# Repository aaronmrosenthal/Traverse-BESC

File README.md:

# TRAVERSE VESC
alpha controller

Based on BESC-G2 VESC

TRAVERSE VESC is licensed under the Creative Commons Attribution-ShareAlike 4.0 International License. To view a copy of this license, visit http://creativecommons.org/licenses/by-sa/4.0/.

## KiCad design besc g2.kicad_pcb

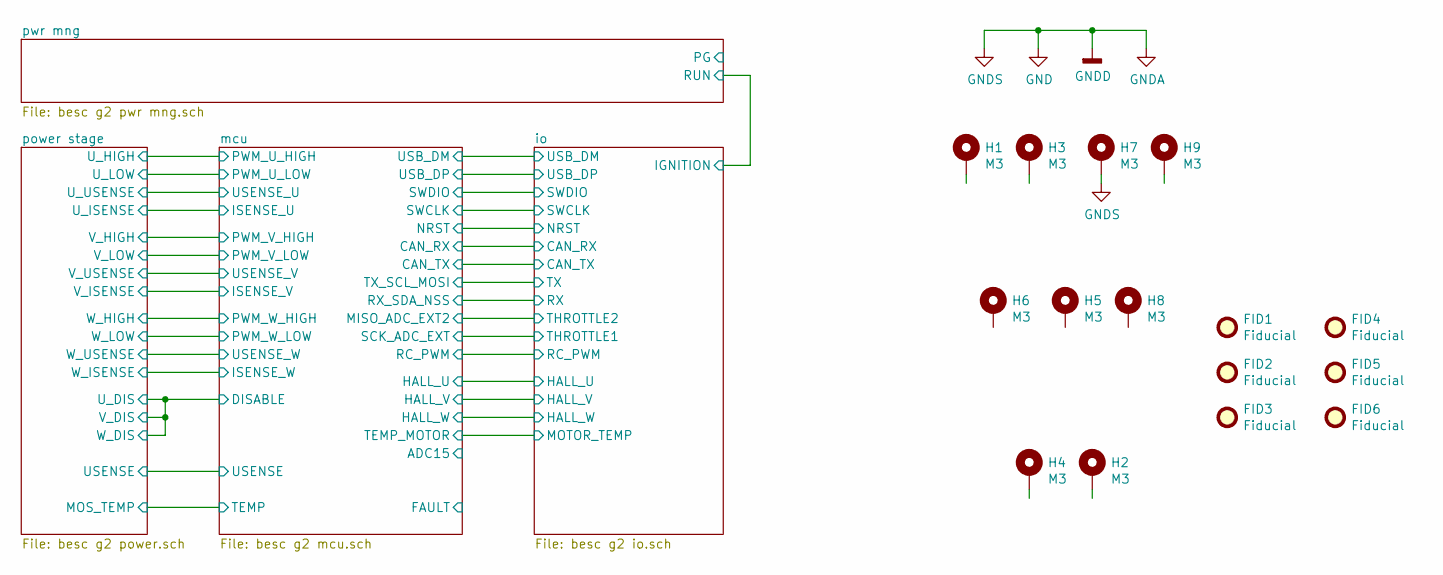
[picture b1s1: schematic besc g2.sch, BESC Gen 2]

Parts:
FID1, FID2, FID3, FID4, FID5, FID6: Fiducial; Fiducial_0.5mm_Mask1.5mm
H1, H2, H3, H4, H5, H6, H7, H8, H9: M3; MountingHole_3.2mm_M3_Pad_Via

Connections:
GND: H7.1; also elsewhere on the board

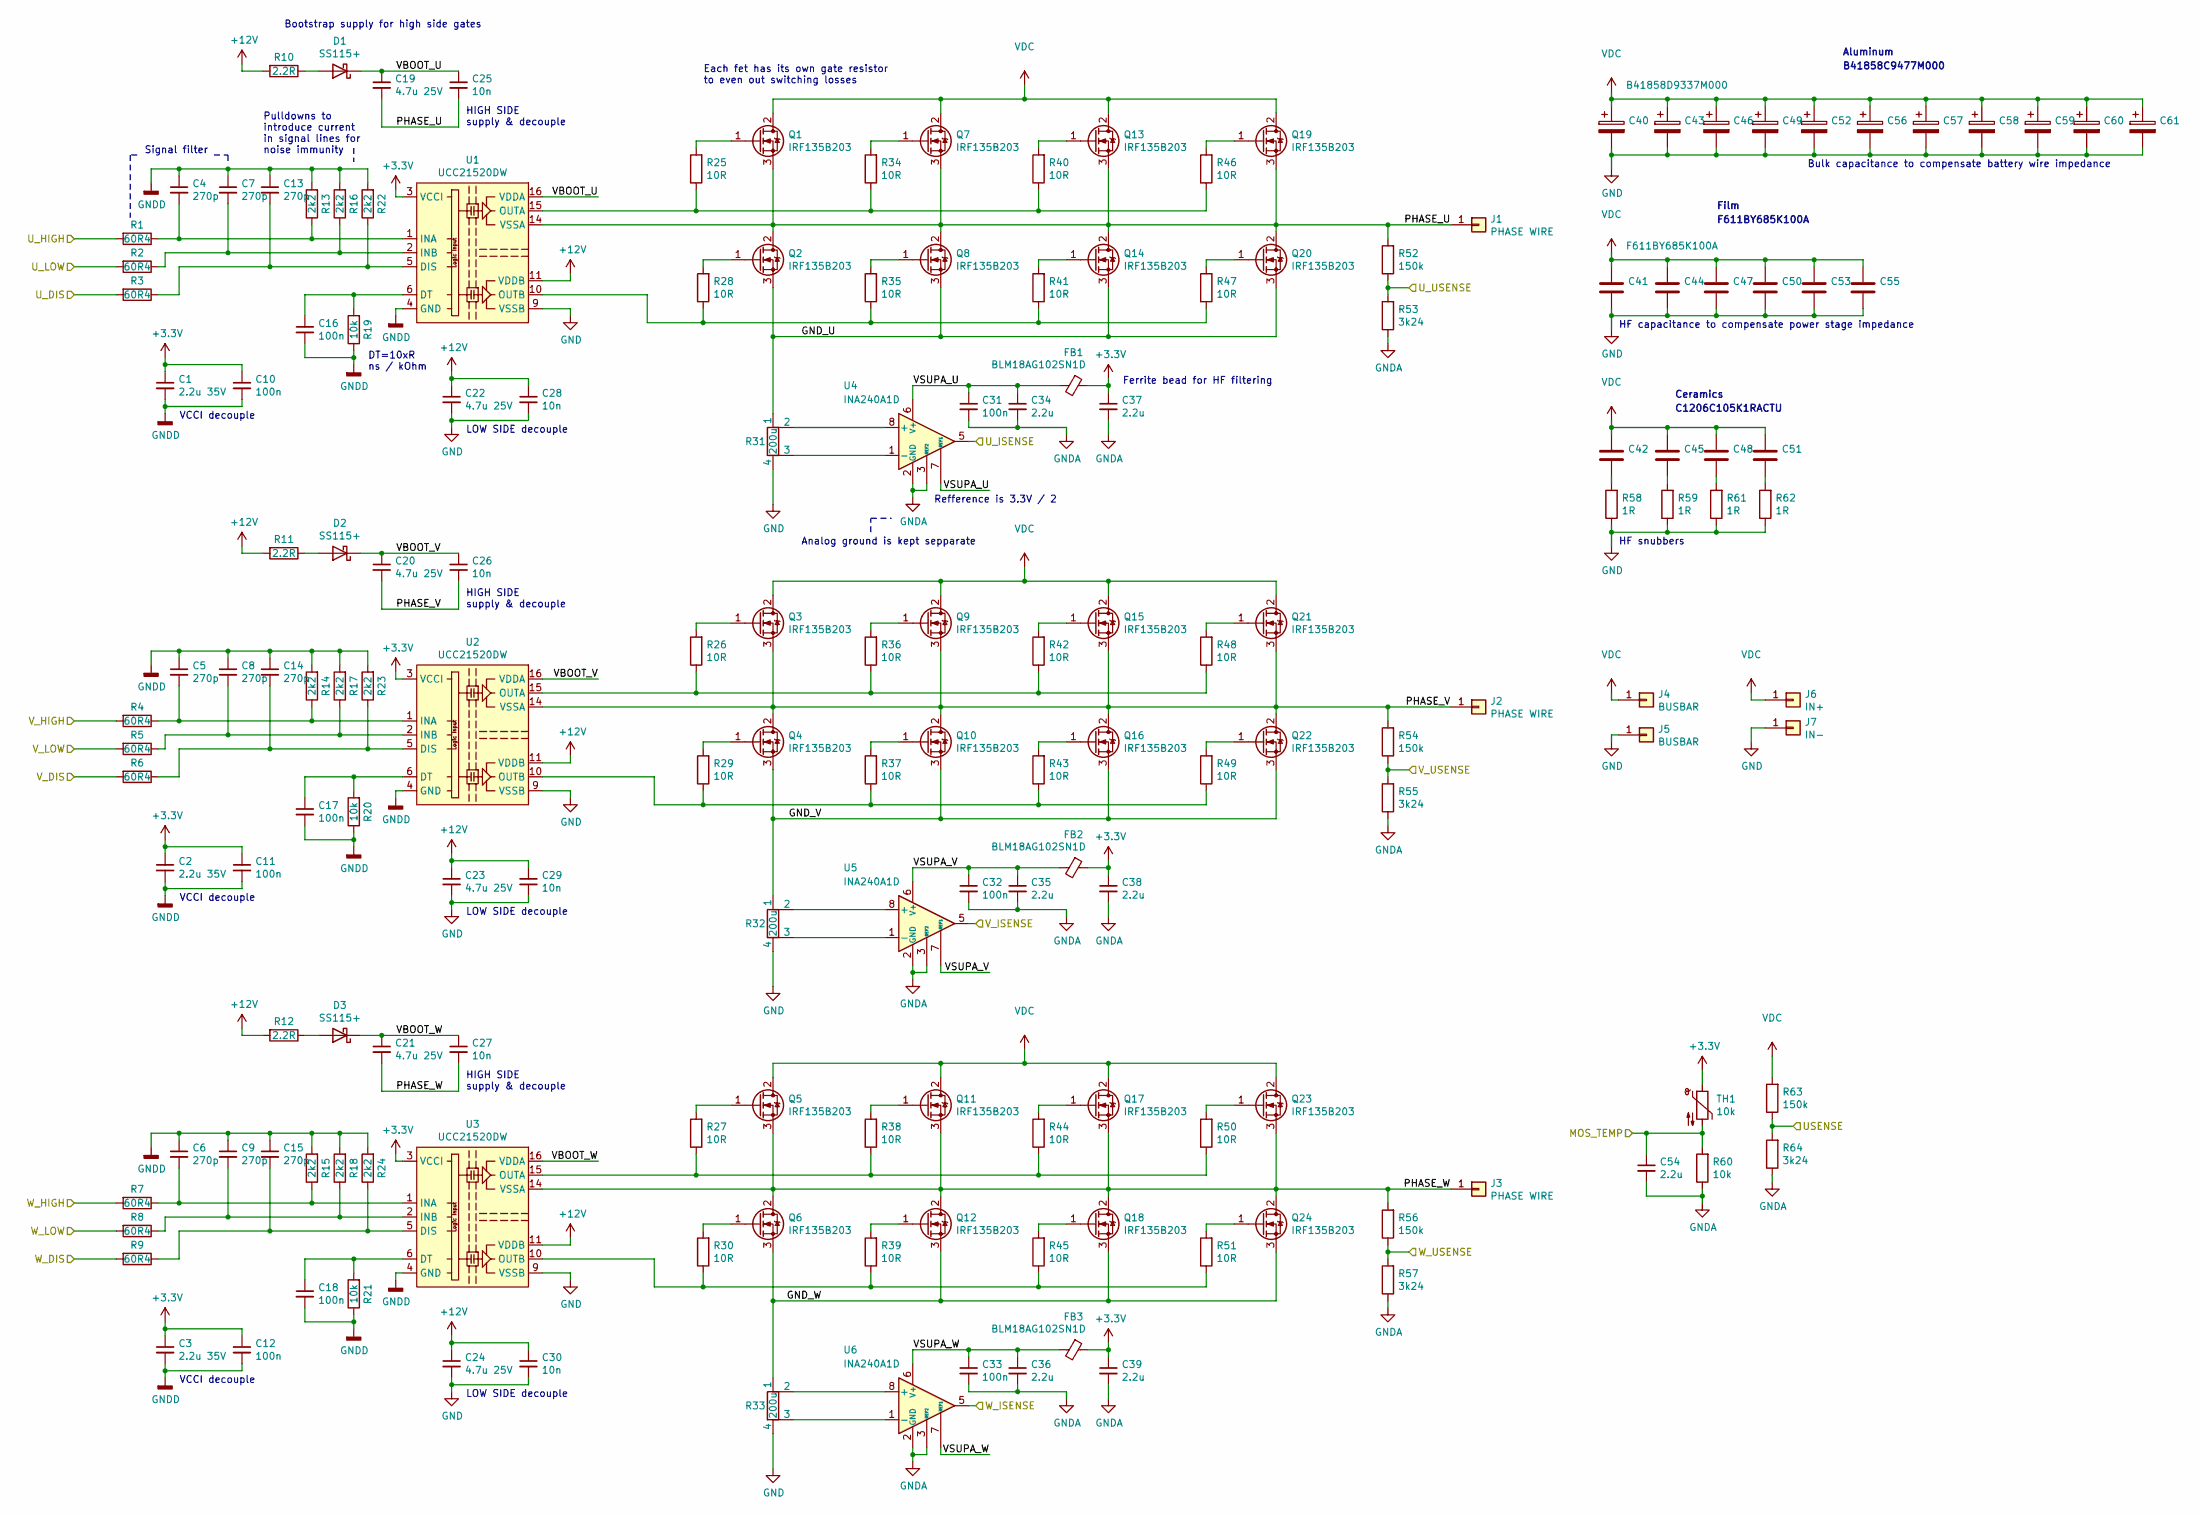
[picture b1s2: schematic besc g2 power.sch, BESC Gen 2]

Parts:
C1, C2, C3: 2.2u 35V; C_0805_2012Metric
C4, C5, C6, C7, C8, C9, C13, C14, C15: 270p; C_0603_1608Metric
C10, C11, C12, C16, C17, C18, C31, C32, C33: 100n; C_0603_1608Metric
C19, C20, C21, C22, C23, C24: 4.7u 25V; C_1206_3216Metric
C25, C26, C27, C28, C29, C30: 10n; C_0603_1608Metric
C34, C35, C36, C37, C38, C39, C54: 2.2u; C_0603_1608Metric
C40, C43, C46, C49, C52, C56, C57, C58, C59, C60, C61: B41858D9337M000; C_Radial_D18.0mm_H25mm_P7.50mm
C41, C44, C47, C50, C53, C55: F611BY685K100A; C_Rect_L18.0mm_W11.0mm_P15.00mm_FKS3_FKP3
C42, C45, C48, C51: C1206C105K1RACTU; C_1206_3216Metric
D1, D2, D3: SS115+; D_SMA
FB1, FB2, FB3: BLM18AG102SN1D; L_0603_1608Metric
J1, J2, J3: PHASE WIRE; 8awg_wirepad
J4, J5: BUSBAR; busbar1
J6: IN+; 8awg_wirepad
J7: IN-; 8awg_wirepad
Q1, Q2, Q3, Q4, Q5, Q6, Q7, Q8, Q9, Q10, Q11, Q12, Q13, Q14, Q15, Q16, Q17, Q18, Q19, Q20, Q21, Q22, Q23, Q24: IRF135B203; TO-220-3_hor_tabup
R1, R2, R3, R4, R5, R6, R7, R8, R9: 60R4; R_0603_1608Metric
R10, R11, R12: 2.2R; R_1206_3216Metric
R13, R14, R15, R16, R17, R18, R22, R23, R24: 2k2; R_0603_1608Metric
R19, R20, R21, R60: 10k; R_0603_1608Metric
R25, R26, R27, R28, R29, R30, R34, R35, R36, R37, R38, R39, R40, R41, R42, R43, R44, R45, R46, R47, R48, R49, R50, R51: 10R; R_0805_2012Metric
R31, R32, R33: 200u; LRMAP5930x
R52, R54, R56, R63: 150k; R_0805_2012Metric
R53, R55, R57, R64: 3k24; R_0603_1608Metric
R58, R59, R61, R62: 1R; R_1206_3216Metric
TH1: 10k; R_0603_1608Metric
U1, U2, U3: UCC21520DW; SOIC-16W_7.5x10.3mm_P1.27mm
U4, U5, U6: INA240A1D; SOIC-8_3.9x4.9mm_P1.27mm

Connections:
+3V3: C1.1, C2.1, C3.1, C10.1, C11.1, C12.1, C37.1, C38.1, C39.1, FB1.1, FB2.1, FB3.1, TH1.1, U1.3 (VCCI), U1.8 (VCCI), U2.3 (VCCI), U2.8 (VCCI), U3.3 (VCCI), U3.8 (VCCI); also elsewhere on the board
+12V: C22.1, C23.1, C24.1, C28.1, C29.1, C30.1, R10.2, R11.2, R12.2, U1.11 (VDDB), U2.11 (VDDB), U3.11 (VDDB); also elsewhere on the board
/mcu/DISABLE: R3.2, R6.2, R9.2; also elsewhere on the board
/mcu/ISENSE_U: U4.5; also elsewhere on the board
/mcu/ISENSE_V: U5.5; also elsewhere on the board
/mcu/ISENSE_W: U6.5; also elsewhere on the board
/mcu/PWM_U_HIGH: R1.2; also elsewhere on the board
/mcu/PWM_U_LOW: R2.2; also elsewhere on the board
/mcu/PWM_V_HIGH: R4.2; also elsewhere on the board
/mcu/PWM_V_LOW: R5.2; also elsewhere on the board
/mcu/PWM_W_HIGH: R7.2; also elsewhere on the board
/mcu/PWM_W_LOW: R8.2; also elsewhere on the board
/mcu/USENSE: R63.1, R64.2; also elsewhere on the board
/mcu/USENSE_U: R52.1, R53.2; also elsewhere on the board
/mcu/USENSE_V: R54.1, R55.2; also elsewhere on the board
/mcu/USENSE_W: R56.1, R57.2; also elsewhere on the board
/power stage/GND_U: Q2.3 (S), Q8.3 (S), Q14.3 (S), Q20.3 (S), R31.1
/power stage/GND_V: Q4.3 (S), Q10.3 (S), Q16.3 (S), Q22.3 (S), R32.1
/power stage/GND_W: Q6.3 (S), Q12.3 (S), Q18.3 (S), Q24.3 (S), R33.1
/power stage/MOS_TEMP: C54.1, R60.2, TH1.2; also elsewhere on the board
/power stage/PHASE_U: C19.2, C25.2, J1.1, Q1.3 (S), Q2.2 (D), Q7.3 (S), Q8.2 (D), Q13.3 (S), Q14.2 (D), Q19.3 (S), Q20.2 (D), R52.2, U1.14 (VSSA)
/power stage/PHASE_V: C20.2, C26.2, J2.1, Q3.3 (S), Q4.2 (D), Q9.3 (S), Q10.2 (D), Q15.3 (S), Q16.2 (D), Q21.3 (S), Q22.2 (D), R54.2, U2.14 (VSSA)
/power stage/PHASE_W: C21.2, C27.2, J3.1, Q5.3 (S), Q6.2 (D), Q11.3 (S), Q12.2 (D), Q17.3 (S), Q18.2 (D), Q23.3 (S), Q24.2 (D), R56.2, U3.14 (VSSA)
/power stage/VBOOT_U: C19.1, C25.1, D1.1 (K), U1.16 (VDDA)
/power stage/VBOOT_V: C20.1, C26.1, D2.1 (K), U2.16 (VDDA)
/power stage/VBOOT_W: C21.1, C27.1, D3.1 (K), U3.16 (VDDA)
/power stage/VSUPA_U: C31.1, C34.1, FB1.2, U4.6 (V+), U4.7 (REF1)
/power stage/VSUPA_V: C32.1, C35.1, FB2.2, U5.6 (V+), U5.7 (REF1)
/power stage/VSUPA_W: C33.1, C36.1, FB3.2, U6.6 (V+), U6.7 (REF1)
GND: C1.2, C2.2, C3.2, C4.1, C5.1, C6.1, C7.1, C8.1, C9.1, C10.2, C11.2, C12.2, C13.1, C14.1, C15.1, C16.2, C17.2, C18.2, C22.2, C23.2, C24.2, C28.2, C29.2, C30.2, C31.2, C32.2, C33.2, C34.2, C35.2, C36.2, C37.2, C38.2, C39.2, C40.2, C41.2, C43.2, C44.2, C46.2, C47.2, C49.2, C50.2, C52.2, C53.2, C54.2, C55.2, C56.2, C57.2, C58.2, C59.2, C60.2, C61.2, J5.1, J7.1, R13.2, R14.2, R15.2, R16.2, R17.2, R18.2, R19.1, R20.1, R21.1, R22.2, R23.2, R24.2, R31.4, R32.4, R33.4, R53.1, R55.1, R57.1, R58.1, R59.1, R60.1, R61.1, R62.1, R64.1, U1.4 (GND), U1.9 (VSSB), U2.4 (GND), U2.9 (VSSB), U3.4 (GND), U3.9 (VSSB), U4.2 (GND), U4.3 (REF2), U4.4 (GND), U5.2 (GND), U5.3 (REF2), U5.4 (GND), U6.2 (GND), U6.3 (REF2), U6.4 (GND); also elsewhere on the board
unnamed: C4.2, R1.1, R13.1, U1.1 (INA)
unnamed: C5.2, R4.1, R14.1, U2.1 (INA)
unnamed: C6.2, R7.1, R15.1, U3.1 (INA)
unnamed: C7.2, R2.1, R16.1, U1.2 (INB)
unnamed: C8.2, R5.1, R17.1, U2.2 (INB)
unnamed: C9.2, R8.1, R18.1, U3.2 (INB)
unnamed: C13.2, R3.1, R22.1, U1.5 (DIS)
unnamed: C14.2, R6.1, R23.1, U2.5 (DIS)
unnamed: C15.2, R9.1, R24.1, U3.5 (DIS)
unnamed: C16.1, R19.2, U1.6 (DT)
unnamed: C17.1, R20.2, U2.6 (DT)
unnamed: C18.1, R21.2, U3.6 (DT)
unnamed: C42.2, R58.2
unnamed: C45.2, R59.2
unnamed: C48.2, R61.2
unnamed: C51.2, R62.2
unnamed: D1.2 (A), R10.1
unnamed: D2.2 (A), R11.1
unnamed: D3.2 (A), R12.1
unnamed: Q1.1 (G), R25.2
unnamed: Q2.1 (G), R28.2
unnamed: Q3.1 (G), R26.2
unnamed: Q4.1 (G), R29.2
unnamed: Q5.1 (G), R27.2
unnamed: Q6.1 (G), R30.2
unnamed: Q7.1 (G), R34.2
unnamed: Q8.1 (G), R35.2
unnamed: Q9.1 (G), R36.2
unnamed: Q10.1 (G), R37.2
unnamed: Q11.1 (G), R38.2
unnamed: Q12.1 (G), R39.2
unnamed: Q13.1 (G), R40.2
unnamed: Q14.1 (G), R41.2
unnamed: Q15.1 (G), R42.2
unnamed: Q16.1 (G), R43.2
unnamed: Q17.1 (G), R44.2
unnamed: Q18.1 (G), R45.2
unnamed: Q19.1 (G), R46.2
unnamed: Q20.1 (G), R47.2
unnamed: Q21.1 (G), R48.2
unnamed: Q22.1 (G), R49.2
unnamed: Q23.1 (G), R50.2
unnamed: Q24.1 (G), R51.2
unnamed: R25.1, R34.1, R40.1, R46.1, U1.15 (OUTA)
unnamed: R26.1, R36.1, R42.1, R48.1, U2.15 (OUTA)
unnamed: R27.1, R38.1, R44.1, R50.1, U3.15 (OUTA)
unnamed: R28.1, R35.1, R41.1, R47.1, U1.10 (OUTB)
unnamed: R29.1, R37.1, R43.1, R49.1, U2.10 (OUTB)
unnamed: R30.1, R39.1, R45.1, R51.1, U3.10 (OUTB)
unnamed: R31.2, U4.8 (+)
unnamed: R31.3, U4.1 (-)
unnamed: R32.2, U5.8 (+)
unnamed: R32.3, U5.1 (-)
unnamed: R33.2, U6.8 (+)
unnamed: R33.3, U6.1 (-)
VDC: C40.1, C41.1, C42.1, C43.1, C44.1, C45.1, C46.1, C47.1, C48.1, C49.1, C50.1, C51.1, C52.1, C53.1, C55.1, C56.1, C57.1, C58.1, C59.1, C60.1, C61.1, J4.1, J6.1, Q1.2 (D), Q3.2 (D), Q5.2 (D), Q7.2 (D), Q9.2 (D), Q11.2 (D), Q13.2 (D), Q15.2 (D), Q17.2 (D), Q19.2 (D), Q21.2 (D), Q23.2 (D), R63.2; also elsewhere on the board

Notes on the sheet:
LOW SIDE decouple
HIGH SIDE supply & decouple
Aluminum
Film
Ceramics
F611BY685K100A
B41858C9477M000
C1206C105K1RACTU
VCCI decouple
DT=10xR ns / kOhm
Refference is 3.3V / 2
Ferrite bead for HF filtering
Each fet has its own gate resistor to even out switching losses
Bulk capacitance to compensate battery wire impedance
HF capacitance to compensate power stage impedance
HF snubbers
Pulldowns to introduce current in signal lines for noise immunity
Bootstrap supply for high side gates
Signal filter
Analog ground is kept sepparate

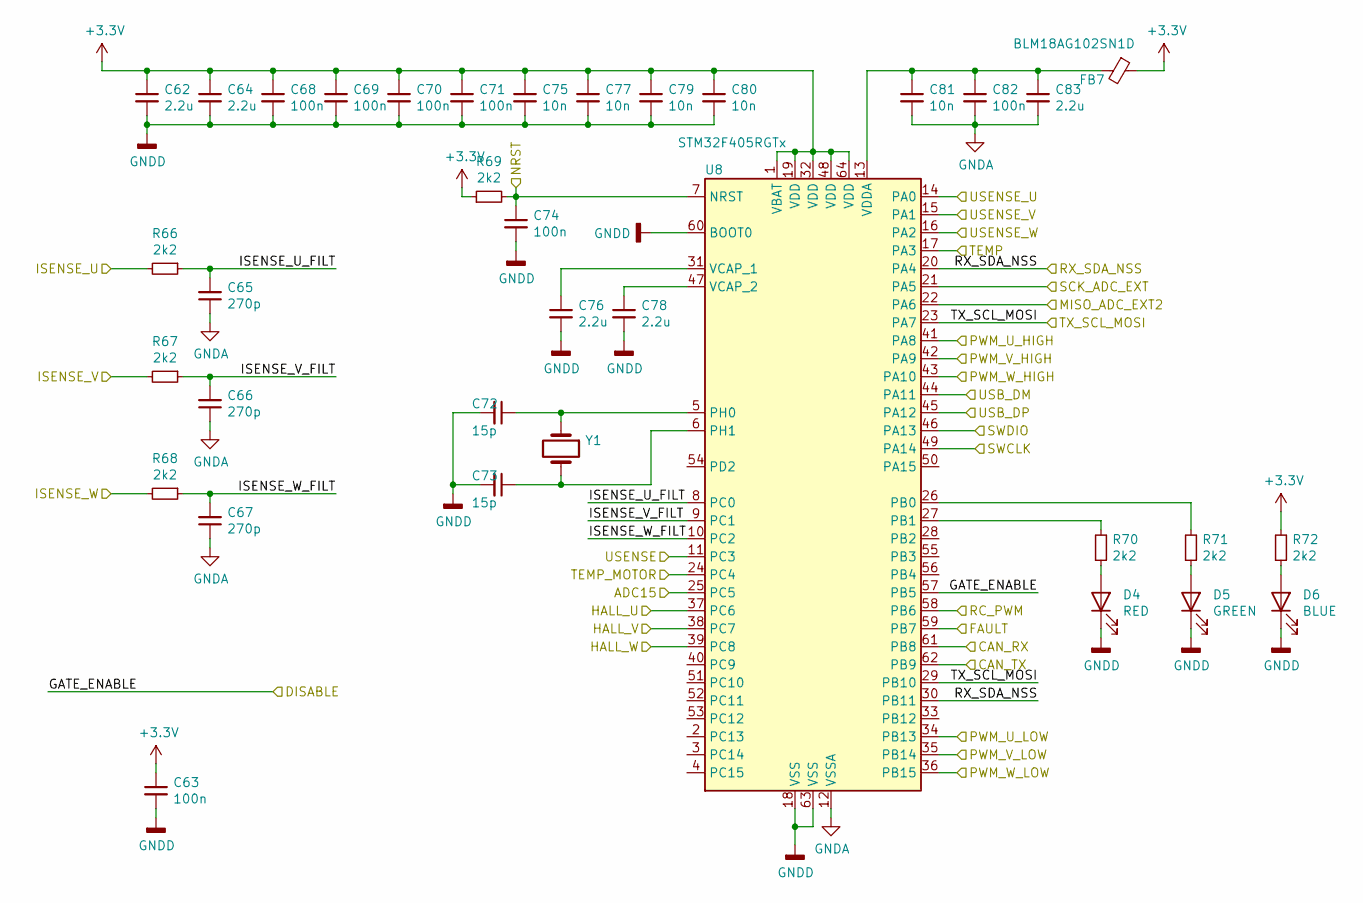
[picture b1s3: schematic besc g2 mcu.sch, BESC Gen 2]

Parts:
C62, C64, C76, C78, C83: 2.2u; C_0603_1608Metric
C63, C68, C69, C70, C71, C74, C82: 100n; C_0603_1608Metric
C65, C66, C67: 270p; C_0603_1608Metric
C72, C73: 15p; C_0603_1608Metric
C75, C77, C79, C80, C81: 10n; C_0603_1608Metric
D4: RED; LED_0603_1608Metric
D5: GREEN; LED_0603_1608Metric
D6: BLUE; LED_0603_1608Metric
FB7: BLM18AG102SN1D; L_0603_1608Metric
R66, R67, R68, R69, R70, R71, R72: 2k2; R_0603_1608Metric
U8: STM32F405RGTx; LQFP-64_10x10mm_P0.5mm
Y1: MCSJK-7I-8.00-18-10-60-B-10; Crystal_SMD_5032-4Pin_5.0x3.2mm

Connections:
+3V3: C62.1, C63.1, C64.1, C68.1, C69.1, C70.1, C71.1, C75.1, C77.1, C79.1, C80.1, FB7.1, R69.1, R72.2, U8.1 (VBAT), U8.19 (VDD), U8.32 (VDD), U8.48 (VDD), U8.64 (VDD); also elsewhere on the board
/io/CAN_RX: U8.61 (PB8); also elsewhere on the board
/io/CAN_TX: U8.62 (PB9); also elsewhere on the board
/io/HALL_U: U8.37 (PC6); also elsewhere on the board
/io/HALL_V: U8.38 (PC7); also elsewhere on the board
/io/HALL_W: U8.39 (PC8); also elsewhere on the board
/io/MOTOR_TEMP: U8.24 (PC4); also elsewhere on the board
/io/NRST: C74.1, R69.2, U8.7 (NRST); also elsewhere on the board
/io/RC_PWM: U8.58 (PB6); also elsewhere on the board
/io/RX: U8.20 (PA4), U8.30 (PB11); also elsewhere on the board
/io/SWCLK: U8.49 (PA14); also elsewhere on the board
/io/SWDIO: U8.46 (PA13); also elsewhere on the board
/io/TX: U8.23 (PA7), U8.29 (PB10); also elsewhere on the board
/io/USB_DM: U8.44 (PA11); also elsewhere on the board
/io/USB_DP: U8.45 (PA12); also elsewhere on the board
/mcu/ADC15: U8.25 (PC5)
/mcu/DISABLE: U8.57 (PB5); also elsewhere on the board
/mcu/FAULT: U8.59 (PB7)
/mcu/ISENSE_U: R66.2; also elsewhere on the board
/mcu/ISENSE_U_FILT: C65.2, R66.1, U8.8 (PC0)
/mcu/ISENSE_V: R67.2; also elsewhere on the board
/mcu/ISENSE_V_FILT: C66.2, R67.1, U8.9 (PC1)
/mcu/ISENSE_W: R68.2; also elsewhere on the board
/mcu/ISENSE_W_FILT: C67.2, R68.1, U8.10 (PC2)
/mcu/MISO_ADC_EXT2: U8.22 (PA6); also elsewhere on the board
/mcu/PWM_U_HIGH: U8.41 (PA8); also elsewhere on the board
/mcu/PWM_U_LOW: U8.34 (PB13); also elsewhere on the board
/mcu/PWM_V_HIGH: U8.42 (PA9); also elsewhere on the board
/mcu/PWM_V_LOW: U8.35 (PB14); also elsewhere on the board
/mcu/PWM_W_HIGH: U8.43 (PA10); also elsewhere on the board
/mcu/PWM_W_LOW: U8.36 (PB15); also elsewhere on the board
/mcu/SCK_ADC_EXT: U8.21 (PA5); also elsewhere on the board
/mcu/USENSE: U8.11 (PC3); also elsewhere on the board
/mcu/USENSE_U: U8.14 (PA0); also elsewhere on the board
/mcu/USENSE_V: U8.15 (PA1); also elsewhere on the board
/mcu/USENSE_W: U8.16 (PA2); also elsewhere on the board
/power stage/MOS_TEMP: U8.17 (PA3); also elsewhere on the board
GND: C62.2, C63.2, C64.2, C65.1, C66.1, C67.1, C68.2, C69.2, C70.2, C71.2, C72.2, C73.2, C74.2, C75.2, C76.2, C77.2, C78.2, C79.2, C80.2, C81.2, C82.2, C83.2, D4.1 (K), D5.1 (K), D6.1 (K), U8.12 (VSSA), U8.18 (VSS), U8.60 (BOOT0), U8.63 (VSS); also elsewhere on the board
unnamed: C72.1, U8.5 (PH0), Y1.1
unnamed: C73.1, U8.6 (PH1), Y1.2
unnamed: C76.1, U8.31 (VCAP_1)
unnamed: C78.1, U8.47 (VCAP_2)
unnamed: C81.1, C82.1, C83.1, FB7.2, U8.13 (VDDA)
unnamed: D4.2 (A), R70.1
unnamed: D5.2 (A), R71.1
unnamed: D6.2 (A), R72.1
unnamed: R70.2, U8.27 (PB1)
unnamed: R71.2, U8.26 (PB0)

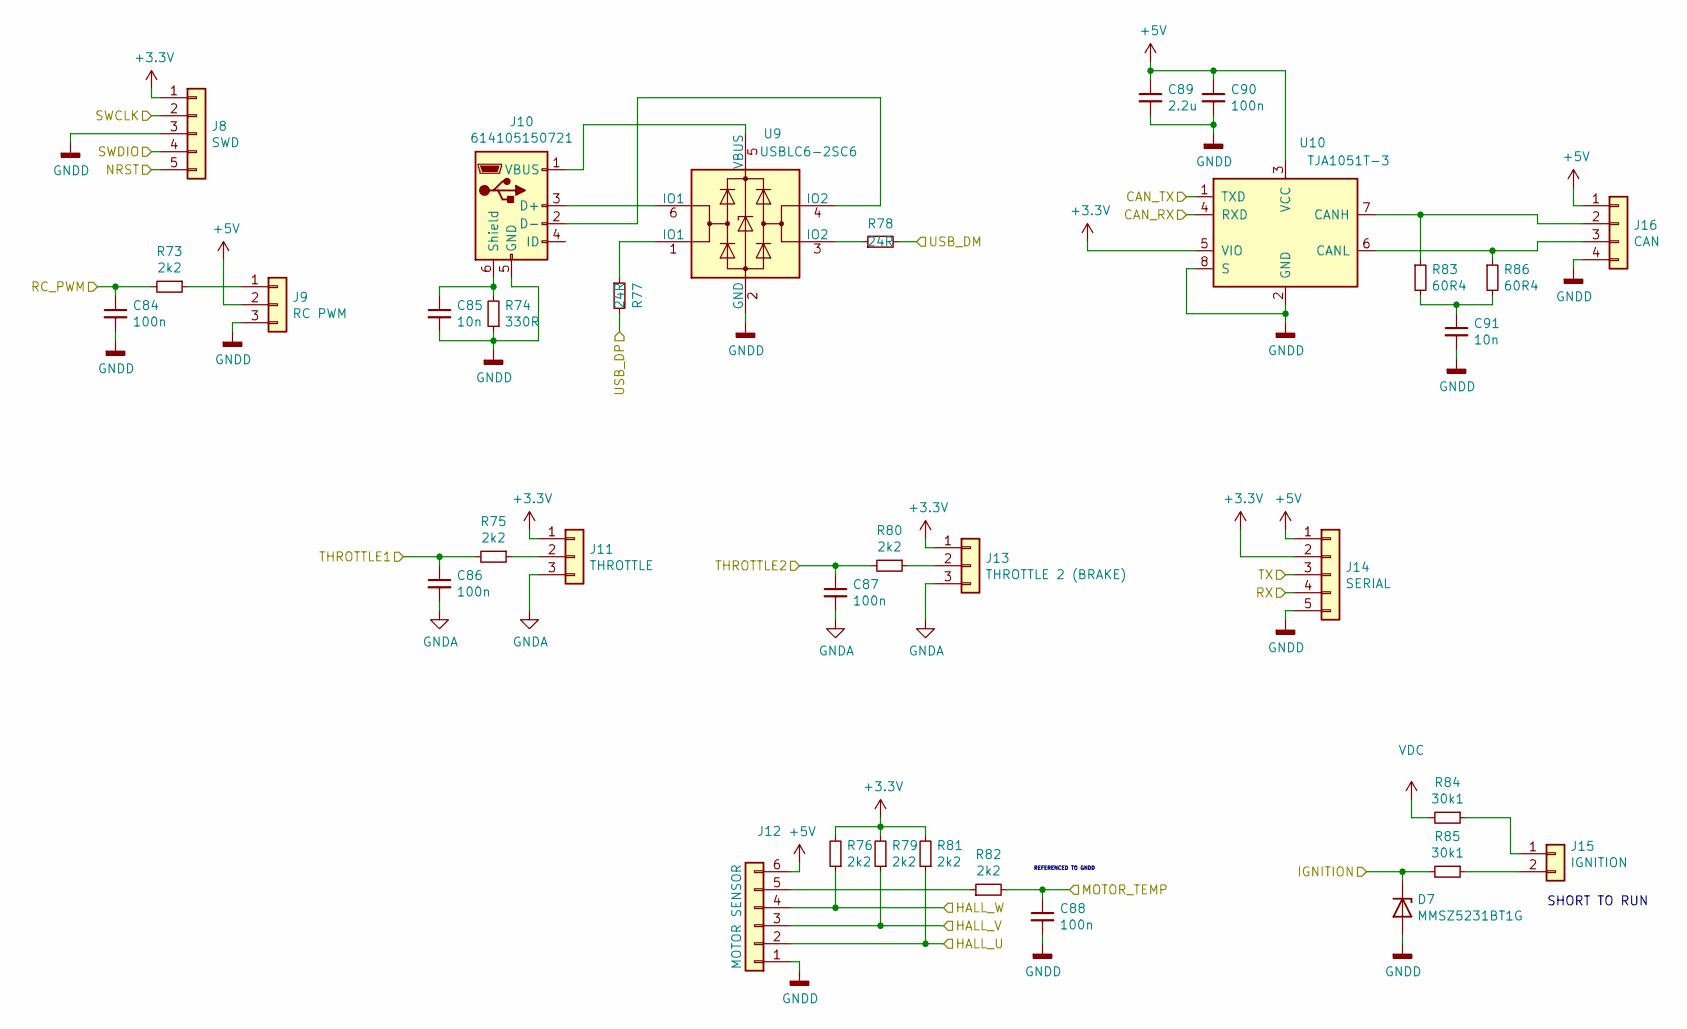
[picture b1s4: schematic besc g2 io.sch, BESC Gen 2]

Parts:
C84, C86, C87, C88, C90: 100n; C_0603_1608Metric
C85, C91: 10n; C_0603_1608Metric
C89: 2.2u; C_0603_1608Metric
D7: MMSZ5231BT1G; D_SOD-123
J8: SWD; PinHeader_1x05_P2.54mm_Vertical
J9: RC PWM; PinHeader_1x03_P2.54mm_Vertical
J10: 614105150721; USB_Micro-B_Wuerth_614105150721_Vertical_CircularHoles
J11: THROTTLE; PinHeader_1x03_P2.54mm_Vertical
J12: MOTOR SENSOR; PinHeader_1x06_P2.54mm_Vertical
J13: THROTTLE 2 (BRAKE); PinHeader_1x03_P2.54mm_Vertical
J14: SERIAL; PinHeader_1x05_P2.54mm_Vertical
J15: IGNITION; PinHeader_1x02_P2.54mm_Vertical
J16: CAN; PinHeader_1x04_P2.54mm_Vertical
R73, R75, R76, R79, R80, R81, R82: 2k2; R_0603_1608Metric
R74: 330R; R_0603_1608Metric
R77, R78: 24R; R_0603_1608Metric
R83, R86: 60R4; R_0603_1608Metric
R84, R85: 30k1; R_0603_1608Metric
U9: USBLC6-2SC6; SOT-666
U10: TJA1051T-3; SOIC-8_3.9x4.9mm_P1.27mm

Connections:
+3V3: J8.1, J11.1, J13.1, J14.2, R76.2, R79.2, R81.2, U10.5 (VIO); also elsewhere on the board
+5V: C89.1, C90.1, J9.2, J12.6, J14.1, J16.1, U10.3 (VCC); also elsewhere on the board
/io/CAN_RX: U10.4 (RXD); also elsewhere on the board
/io/CAN_TX: U10.1 (TXD); also elsewhere on the board
/io/HALL_U: J12.2, R81.1; also elsewhere on the board
/io/HALL_V: J12.3, R79.1; also elsewhere on the board
/io/HALL_W: J12.4, R76.1; also elsewhere on the board
/io/IGNITION: D7.1 (K), R85.2; also elsewhere on the board
/io/MOTOR_TEMP: C88.1, R82.2; also elsewhere on the board
/io/NRST: J8.5; also elsewhere on the board
/io/RC_PWM: C84.1, R73.2; also elsewhere on the board
/io/RX: J14.4; also elsewhere on the board
/io/SWCLK: J8.2; also elsewhere on the board
/io/SWDIO: J8.4; also elsewhere on the board
/io/TX: J14.3; also elsewhere on the board
/io/USB_DM: R78.2; also elsewhere on the board
/io/USB_DP: R77.2; also elsewhere on the board
/mcu/MISO_ADC_EXT2: C87.1, R80.2; also elsewhere on the board
/mcu/SCK_ADC_EXT: C86.1, R75.2; also elsewhere on the board
GND: C84.2, C85.2, C86.2, C87.2, C88.2, C89.2, C90.2, C91.2, D7.2 (A), J8.3, J9.3, J10.5 (GND), J11.3, J12.1, J13.3, J14.5, J16.4, R74.1, U9.2 (GND), U10.2 (GND), U10.8 (S); also elsewhere on the board
unnamed: C85.1, J10.6 (Shield), R74.2
unnamed: C91.1, R83.2, R86.2
unnamed: J9.1, R73.1
unnamed: J10.1 (VBUS), U9.5 (VBUS)
unnamed: J10.2 (D-), U9.4 (IO2)
unnamed: J10.3 (D+), U9.6 (IO1)
unnamed: J11.2, R75.1
unnamed: J12.5, R82.1
unnamed: J13.2, R80.1
unnamed: J15.1, R84.1
unnamed: J15.2, R85.1
unnamed: J16.2, R83.1, U10.7 (CANH)
unnamed: J16.3, R86.1, U10.6 (CANL)
unnamed: R77.1, U9.1 (IO1)
unnamed: R78.1, U9.3 (IO2)
VDC: R84.2; also elsewhere on the board

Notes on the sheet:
REFERENCED TO GNDD
SHORT TO RUN

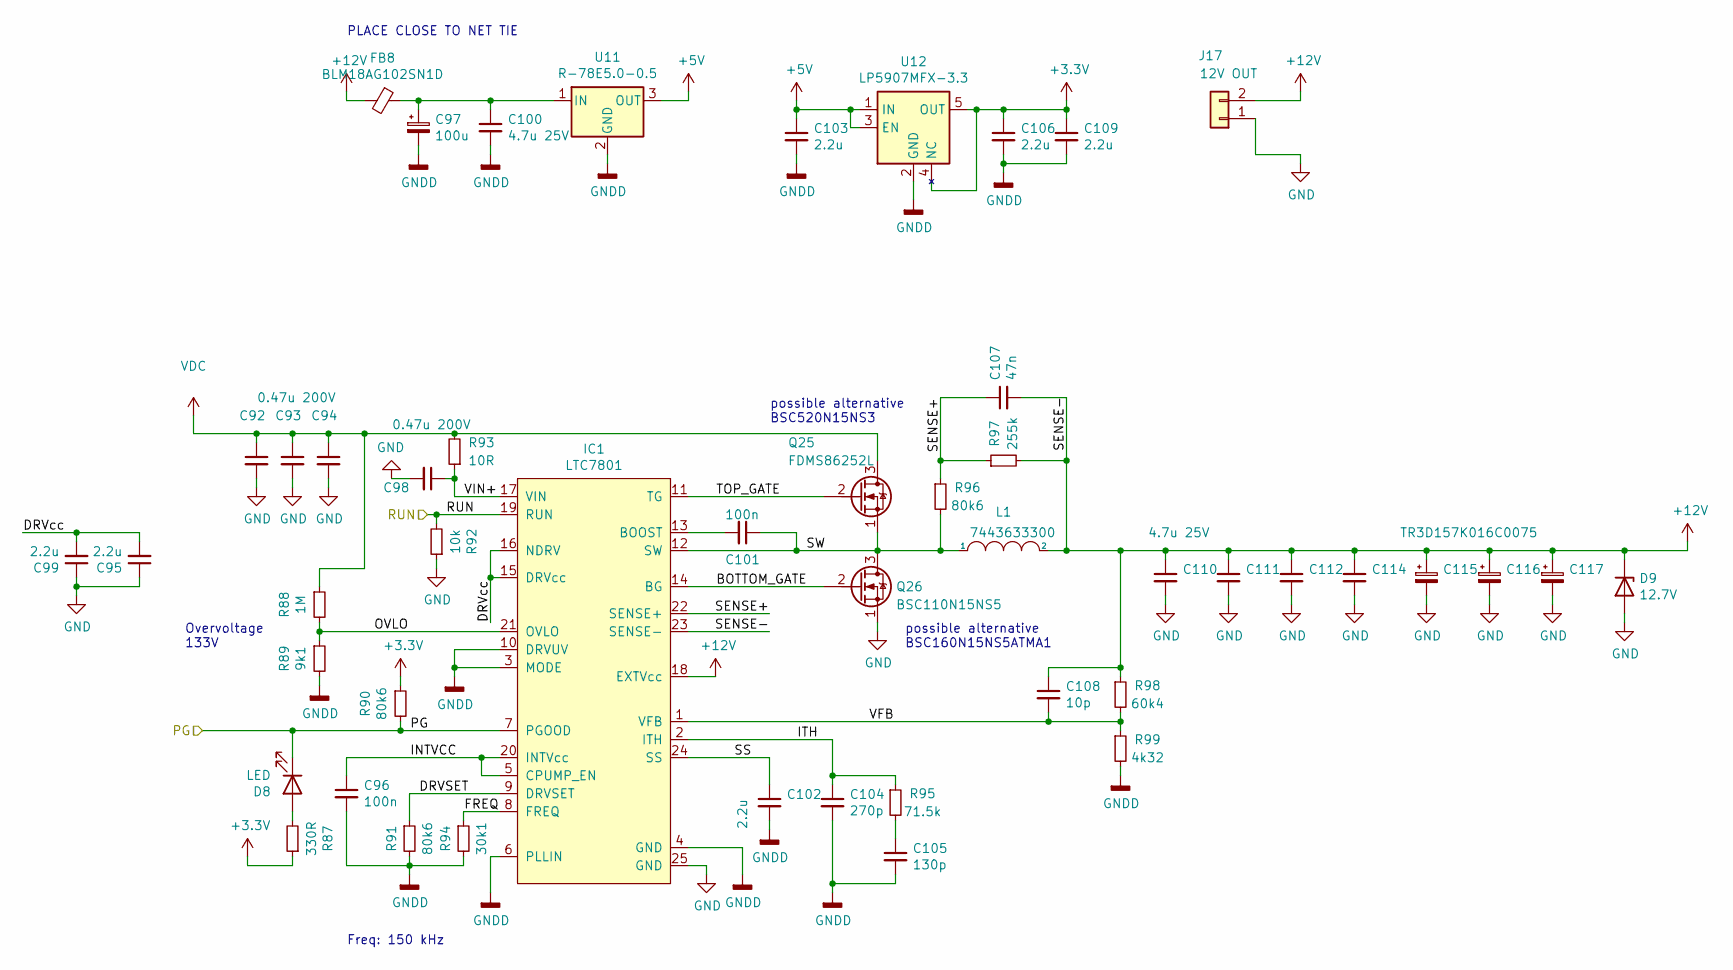
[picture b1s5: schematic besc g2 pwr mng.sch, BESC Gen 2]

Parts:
C92, C93, C94, C98: 0.47u 200V; C_1210_3225Metric
C95, C99, C102, C103, C106, C109: 2.2u; C_0603_1608Metric
C96, C101: 100n; C_0603_1608Metric
C97: 100u; CP_EIA-6032-28_Kemet-C; PART TAJD107M016RNJ
C100, C110, C111, C112, C114: 4.7u 25V; C_1206_3216Metric
C104: 270p; C_0603_1608Metric
C105: 130p; C_0603_1608Metric
C107: 47n; C_0603_1608Metric
C108: 10p; C_0603_1608Metric
C115, C116, C117: TR3D157K016C0075; CP_EIA-7343-31_Kemet-D
D8: LED; LED_0603_1608Metric
D9: 12.7V; D_SMA
FB8: BLM18AG102SN1D; L_0603_1608Metric
IC1: LTC7801; QFN-24-1EP_4x5mm_P0.5mm_EP2.65x3.65mm
J17: 12V OUT; AMASS_XT30U-M_1x02_P5.0mm_Vertical
L1: 7443633300; WE-HCF-2013
Q25: FDMS86252L; TDSON-8-MOS
Q26: BSC110N15NS5; TDSON-8-MOS
R87: 330R; R_0603_1608Metric
R88: 1M; R_0603_1608Metric
R89: 9k1; R_0603_1608Metric
R90, R91, R96: 80k6; R_0603_1608Metric
R92: 10k; R_0603_1608Metric
R93: 10R; R_0805_2012Metric
R94: 30k1; R_0603_1608Metric
R95: 71.5k; R_0603_1608Metric
R97: 255k; R_0603_1608Metric
R98: 60k4; R_0603_1608Metric
R99: 4k32; R_0603_1608Metric
U11: R-78E5.0-0.5; Converter_DCDC_RECOM_R-78E-0.5_THT
U12: LP5907MFX-3.3; SOT-23-5

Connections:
+3V3: C106.1, C109.1, R87.1, R90.1, U12.4 (NC), U12.5 (OUT); also elsewhere on the board
+5V: C103.1, U11.3 (OUT), U12.1 (IN), U12.3 (EN); also elsewhere on the board
+12V: C107.2, C108.1, C110.1, C111.1, C112.1, C114.1, C115.1, C116.1, C117.1, D9.1 (K), FB8.2, IC1.18 (EXTVcc), IC1.23 (SENSE-), J17.2, L1.2, R97.2, R98.1; also elsewhere on the board
/io/IGNITION: IC1.19 (RUN), R92.2; also elsewhere on the board
/pwr mng/BOTTOM_GATE: IC1.14 (BG), Q26.2 (G)
/pwr mng/DRVSET: IC1.9 (DRVSET), R91.1
/pwr mng/DRVcc: C95.2, C99.2, IC1.15 (DRVcc), IC1.16 (NDRV)
/pwr mng/FREQ: IC1.8 (FREQ), R94.1
/pwr mng/INTVCC: C96.1, IC1.5 (CPUMP_EN), IC1.20 (INTVcc)
/pwr mng/ITH: C104.1, IC1.2 (ITH), R95.1
/pwr mng/OVLO: IC1.21 (OVLO), R88.2, R89.1
/pwr mng/PG: D8.1 (K), IC1.7 (PGOOD), R90.2
/pwr mng/SENSE+: C107.1, IC1.22 (SENSE+), R96.1, R97.1
/pwr mng/SS: C102.1, IC1.24 (SS)
/pwr mng/SW: C101.1, IC1.12 (SW), L1.1, Q25.1 (S), Q26.3 (D), R96.2
/pwr mng/TOP_GATE: IC1.11 (TG), Q25.2 (G)
/pwr mng/VFB: C108.2, IC1.1 (VFB), R98.2, R99.1
/pwr mng/VIN+: C98.1, IC1.17 (VIN), R93.1
GND: C92.2, C93.2, C94.2, C95.1, C96.2, C97.2, C98.2, C99.1, C100.2, C102.2, C103.2, C104.2, C105.2, C106.2, C109.2, C110.2, C111.2, C112.2, C114.2, C115.2, C116.2, C117.2, D9.2 (A), IC1.3 (MODE), IC1.4 (GND), IC1.6 (PLLIN), IC1.10 (DRVUV), IC1.25 (GND), J17.1, Q26.1 (S), R89.2, R91.2, R92.1, R94.2, R99.2, U11.2 (GND), U12.2 (GND); also elsewhere on the board
unnamed: C97.1, C100.1, FB8.1, U11.1 (IN)
unnamed: C101.2, IC1.13 (BOOST)
unnamed: C105.1, R95.2
unnamed: D8.2 (A), R87.2
VDC: C92.1, C93.1, C94.1, Q25.3 (D), R88.1, R93.2; also elsewhere on the board

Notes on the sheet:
PLACE CLOSE TO NET TIE
Overvoltage 133V
Freq: 150 kHz
possible alternative BSC160N15NS5ATMA1
possible alternative BSC520N15NS3

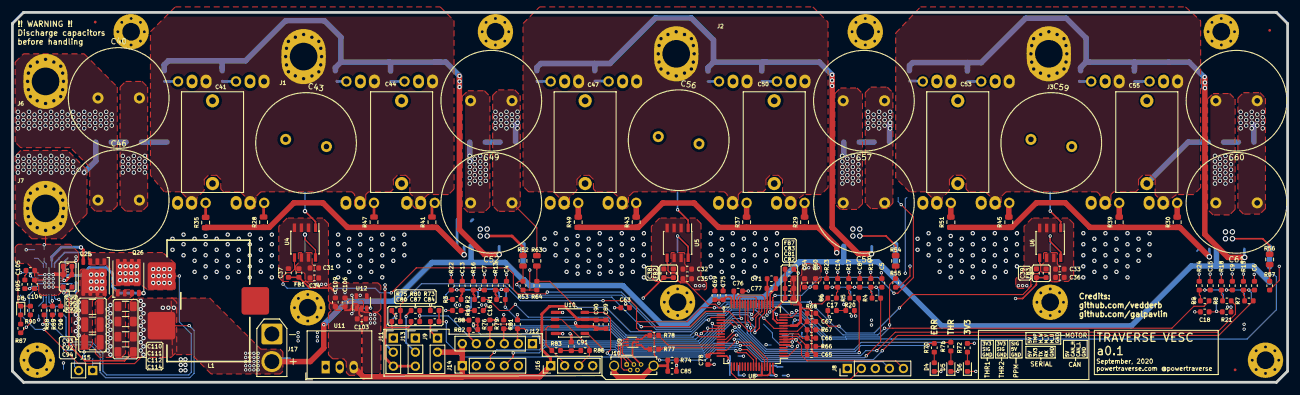
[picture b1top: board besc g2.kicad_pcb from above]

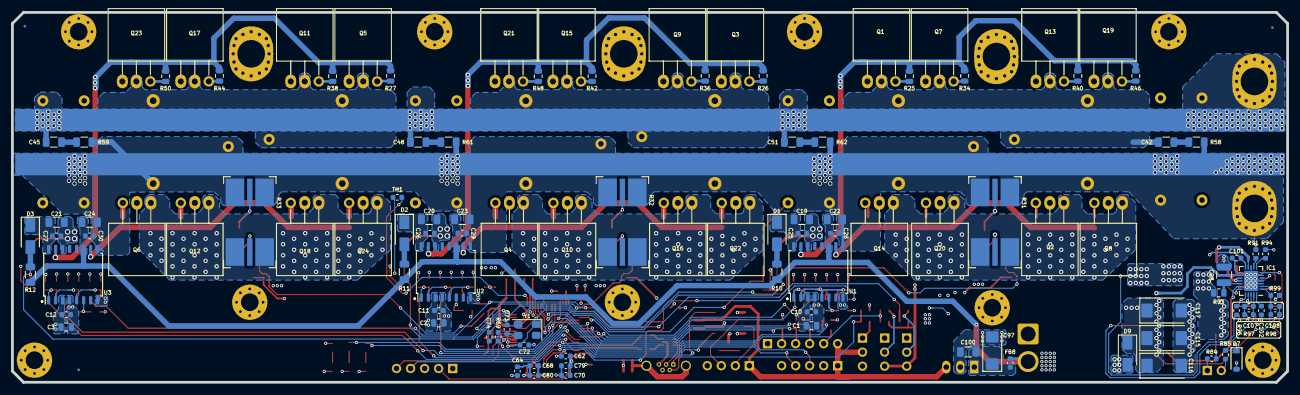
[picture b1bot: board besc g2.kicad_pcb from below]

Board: 4 copper layers, 231.0 x 67.0 mm, 301 parts (114 on the bottom side), 150 nets.

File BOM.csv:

Id;Designator;Package;Quantity;Designation;Supplier and ref
1;C61,C60,C59,C58,C57,C56,C52,C49,C46,C43,C40;C_Radial_D18.0mm_H25mm_P7.50mm;11;B41858D9337M000;
2;J1,J2,J3;8awg_wirepad;3;PHASE WIRE;
3;J6;8awg_wirepad;1;IN+;
4;J7;8awg_wirepad;1;IN-;
5;R93,R25,R26,R27,R28,R29,R30,R34,R35,R36,R37,R38,R39,R40,R41,R42,R43,R44,R45,R46,R47,R48,R49,R50,R51;R_0805_2012Metric;25;10R;
6;C98,C94,C93,C92;C_1210_3225Metric;4;0.47u 200V;
7;FID6,FID5,FID4,FID3,FID2,FID1;Fiducial_0.5mm_Mask1.5mm;6;Fiducial;
8;C95,C54,C102,C99,C34,C35,C36,C37,C38,C39,C62,C64,C76,C78,C83,C89,C103,C106,C109;C_0603_1608Metric;19;2.2u;
9;C30,C29,C28,C27,C26,C25,C75,C77,C79,C80,C81,C85,C91;C_0603_1608Metric;13;10n;
10;C3,C2,C1;C_0805_2012Metric;3;2.2u 35V;
11;C11,C12,C10,C101,C96,C18,C17,C16,C31,C32,C33,C63,C68,C69,C70,C71,C74,C82,C84,C86,C90,C87,C88;C_0603_1608Metric;23;100n;
12;L1;WE-HCF-2013;1;7443633300;
13;J4,J5;busbar1;2;BUSBAR;
14;R31,R32,R33;LRMAP5930x;3;200u;
15;Y1;Crystal_SMD_5032-4Pin_5.0x3.2mm;1;MCSJK-7I-8.00-18-10-60-B-10;
16;Q4,Q24,Q23,Q22,Q21,Q20,Q19,Q18,Q17,Q16,Q15,Q14,Q13,Q12,Q11,Q10,Q9,Q8,Q7,Q6,Q5,Q3,Q2,Q1;TO-220-3_hor_tabup;24;IRF135B203;
17;U9;SOT-666;1;USBLC6-2SC6;
18;TH1,R60,R92,R21,R20,R19;R_0603_1608Metric;6;10k;
19;J10;USB_Micro-B_Wuerth_614105150721_Vertical_CircularHoles;1;6,14105E+11;
20;;;1;;
21;U12;SOT-23-5;1;LP5907MFX-3.3;
22;J11;PinHeader_1x03_P2.54mm_Vertical;1;THROTTLE;
23;R63,R56,R54,R52;R_0805_2012Metric;4;150k;
24;J17;AMASS_XT30U-M_1x02_P5.0mm_Vertical;1;12V OUT;
25;D7;D_SOD-123;1;MMSZ5231BT1G;
26;C100,C114,C112,C111,C110,C24,C23,C21,C20,C19,C22;C_1206_3216Metric;11;4.7u 25V;
27;U11;Converter_DCDC_RECOM_R-78E-0.5_THT;1;R-78E5.0-0.5;
28;D9;D_SMA;1;12.7V;
29;D3,D2,D1;D_SMA;3;SS115+;
30;U3,U2,U1;SOIC-16W_7.5x10.3mm_P1.27mm;3;UCC21520DW;
31;Q25;TDSON-8-MOS;1;FDMS86252L;
32;R97;R_0603_1608Metric;1;255k;
33;R96,R91,R90;R_0603_1608Metric;3;80k6;
34;C107;C_0603_1608Metric;1;47n;
35;R62,R61,R59,R58;R_1206_3216Metric;4;1R;
36;Q26;TDSON-8-MOS;1;BSC110N15NS5;
37;R99;R_0603_1608Metric;1;4k32;
38;R98;R_0603_1608Metric;1;60k4;
39;R95;R_0603_1608Metric;1;71.5k;
40;R94,R85,R84;R_0603_1608Metric;3;30k1;
41;R89;R_0603_1608Metric;1;9k1;
42;R88;R_0603_1608Metric;1;1M;
43;R87,R74;R_0603_1608Metric;2;330R;
44;IC1;QFN-24-1EP_4x5mm_P0.5mm_EP2.65x3.65mm;1;LTC7801;
45;D8;LED_0603_1608Metric;1;LED;
46;C117,C116,C115;CP_EIA-7343-31_Kemet-D;3;TR3D157K016C0075;
47;C108;C_0603_1608Metric;1;10p;
48;C105;C_0603_1608Metric;1;130p;
49;C104,C15,C14,C13,C9,C8,C6,C5,C4,C7,C65,C67;C_0603_1608Metric;12;270p;
50;J15;PinHeader_1x02_P2.54mm_Vertical;1;IGNITION;
51;R24,R23,R22,R18,R17,R15,R14,R13,R16,R67,R68,R69,R70,R71,R72,R73,R75,R76,R79,R80,R81,R82;R_0603_1608Metric;22;2k2;
52;R12,R11,R10;R_1206_3216Metric;3;2.2R;
53;R9,R8,R7,R6,R5,R4,R3,R1,R2,R83,R86;R_0603_1608Metric;11;60R4;
54;H8,H5,H6,H4,H2,H1,H3,H7,H9;MountingHole_3.2mm_M3_Pad_Via;9;M3;
55;C41,C44,C47,C50,C53,C55;C_Rect_L18.0mm_W11.0mm_P15.00mm_FKS3_FKP3;6;F611BY685K100A;
56;C42,C45,C48,C51;C_1206_3216Metric;4;C1206C105K1RACTU;
57;R66;C_0603_1608Metric;1;2k2;
58;C72,C73;C_0603_1608Metric;2;15p;
59;D4;LED_0603_1608Metric;1;RED;
60;D5;LED_0603_1608Metric;1;GREEN;
61;D6;LED_0603_1608Metric;1;BLUE;
62;FB1,FB2,FB3,FB7,FB8;L_0603_1608Metric;5;BLM18AG102SN1D;
63;R53,R55,R57,R64;R_0603_1608Metric;4;3k24;
64;C66;R_0603_1608Metric;1;270p;
65;R77,R78;R_0603_1608Metric;2;24R;
66;U4,U5,U6;SOIC-8_3.9x4.9mm_P1.27mm;3;INA240A1D;
67;U8;LQFP-64_10x10mm_P0.5mm;1;STM32F405RGTx;
68;U10;SOIC-8_3.9x4.9mm_P1.27mm;1;TJA1051T-3;
69;C97;CP_EIA-6032-28_Kemet-C;1;100u;
70;J8;PinHeader_1x05_P2.54mm_Vertical;1;SWD;
71;J9;PinHeader_1x03_P2.54mm_Vertical;1;RC PWM;
72;J12;PinHeader_1x06_P2.54mm_Vertical;1;MOTOR SENSOR;
73;J13;PinHeader_1x03_P2.54mm_Vertical;1;THROTTLE 2 (BRAKE);
74;J14;PinHeader_1x05_P2.54mm_Vertical;1;SERIAL;
75;J16;PinHeader_1x04_P2.54mm_Vertical;1;CAN;

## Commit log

2020-09-27 Re-label
    Updated silkscreen label
2020-09-27 Credits
2020-09-27 R66C66
    Switch R66 C66 Position
2020-09-28 BOM csv added
2020-10-08 Fix component label
2020-10-12 u7 bug fixes
2020-10-13 edit silkscreen label
2020-10-13 updated gerber files
2020-10-13 BOM Gerber updates
2020-10-31 Nikolay Sirkiza
